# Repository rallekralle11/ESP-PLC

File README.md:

# ESP-PLC
Mostly designed this to learn more about PLCs myself. It's not made to any indistrial standard as i can't even afford those standards documents.

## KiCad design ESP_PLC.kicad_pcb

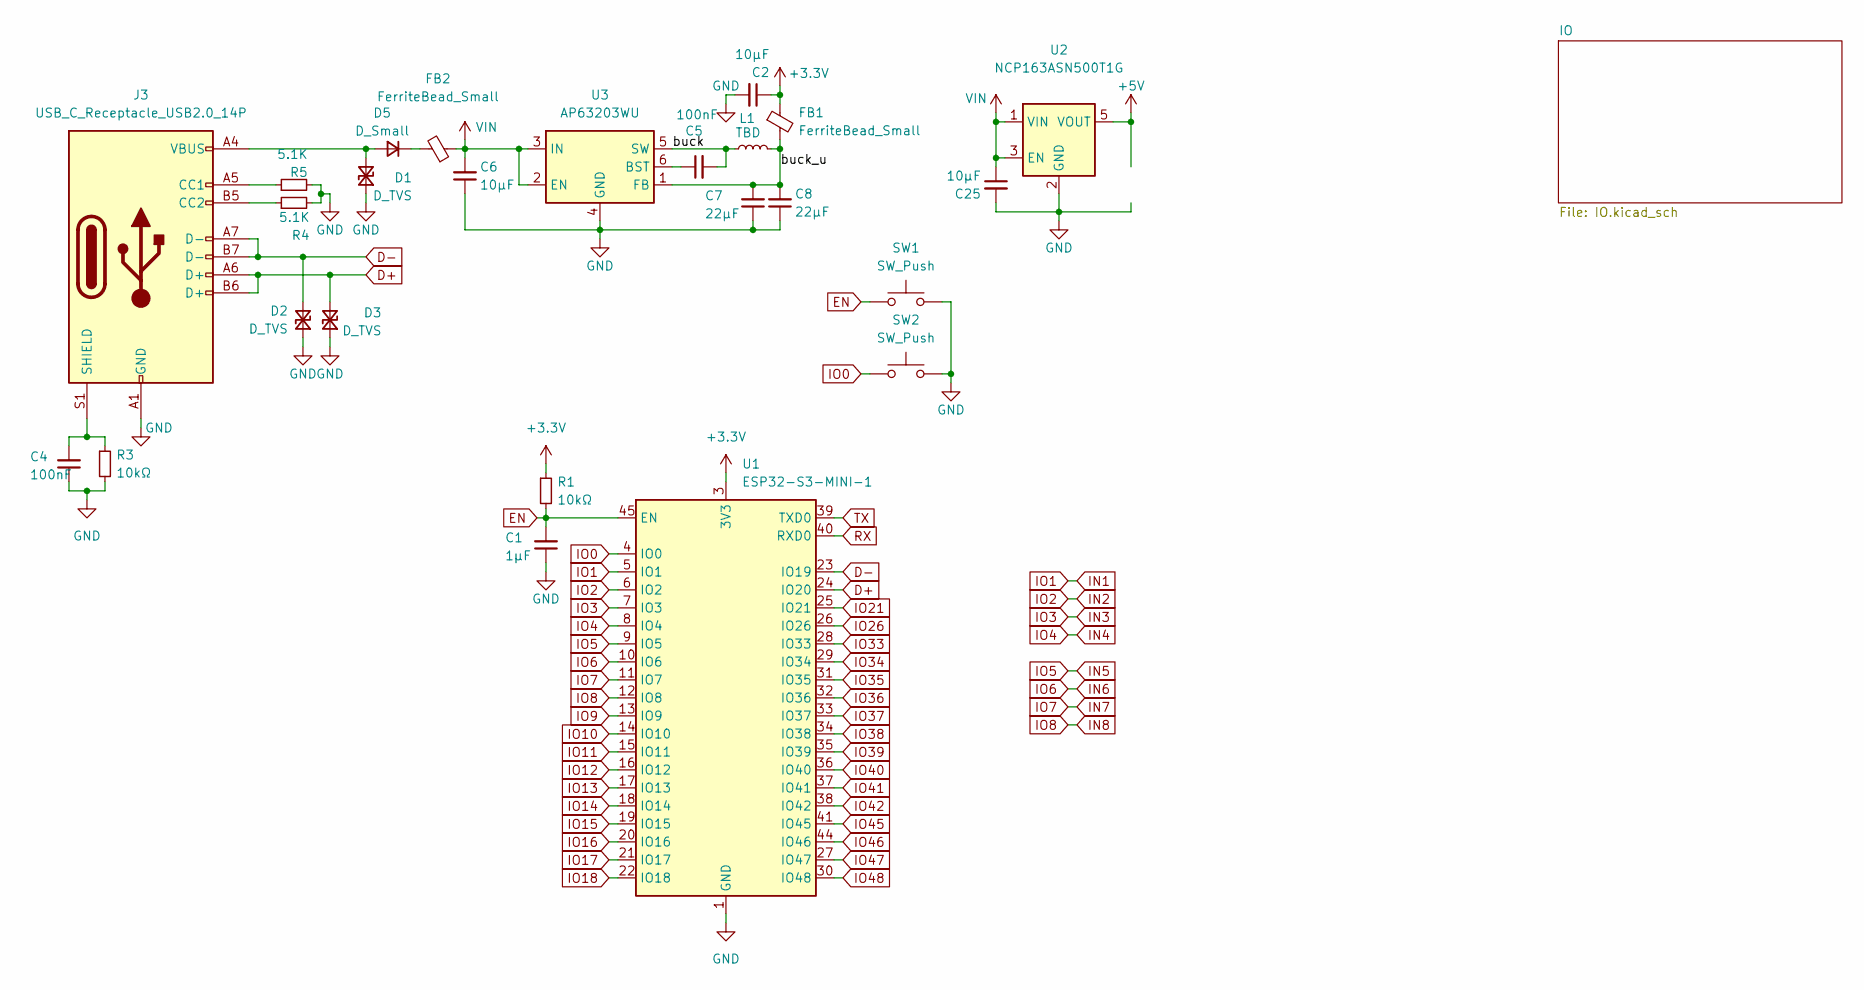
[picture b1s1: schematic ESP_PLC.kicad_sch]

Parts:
C1: 1µF; C_0402_1005Metric
C2, C6, C25: 10µF; C_0805_2012Metric
C4, C5: 100nF; C_0402_1005Metric
C7, C8: 22µF; C_0805_2012Metric
D1, D2, D3: D_TVS; TVS_dubbel
D5: D_Small; D_SOD-323
FB1, FB2: FerriteBead_Small; L_0402_1005Metric
J3: USB_C_Receptacle_USB2.0_14P; USB_C_Receptacle_G-Switch_GT-USB-7010ASV
L1: TBD; L_Abracon_ASPI-0425
R1, R3: 10kΩ; R_0402_1005Metric
R4, R5: 5.1K; R_0402_1005Metric
SW1, SW2: SW_Push; SW_Push_SPST_NO_Alps_SKRK
U1: ESP32-S3-MINI-1; ESP32-S2-MINI-1
U2: NCP163ASN500T1G; SOT-23-5
U3: AP63203WU; TSOT-23-6

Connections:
+3.3V: C2.1, FB1.1, R1.1, U1.3 (3V3); also elsewhere on the board
+5V: U2.5 (VOUT); also elsewhere on the board
/buck: C5.2, L1.1, U3.5 (SW)
/buck_u: C7.2, C8.2, FB1.2, L1.2, U3.1 (FB)
D+: D3.2 (A2), J3.A6 (D+), J3.B6 (D+), U1.24 (IO20)
D-: D2.2 (A2), J3.A7 (D-), J3.B7 (D-), U1.23 (IO19)
EN: C1.2, R1.2, SW1.1, U1.45 (EN)
GND: C1.1, C2.2, C4.1, C6.1, C7.1, C8.1, C25.2, D1.1 (A1), D2.1 (A1), D3.1 (A1), J3.A1 (GND), J3.A12 (GND), J3.B1 (GND), J3.B12 (GND), R3.2, R4.2, R5.2, SW1.2, SW2.2, U1.1 (GND), U1.2 (GND), U1.42 (GND), U1.43 (GND), U1.46 (GND), U1.47 (GND), U1.48 (GND), U1.49 (GND), U1.50 (GND), U1.51 (GND), U1.52 (GND), U1.53 (GND), U1.54 (GND), U1.55 (GND), U1.56 (GND), U1.57 (GND), U1.58 (GND), U1.59 (GND), U1.60 (GND), U1.61 (GND), U1.62 (GND), U1.63 (GND), U1.64 (GND), U1.65 (GND), U2.2 (GND), U3.4 (GND); also elsewhere on the board
IN1: U1.5 (IO1); also elsewhere on the board
IN2: U1.6 (IO2); also elsewhere on the board
IN3: U1.7 (IO3); also elsewhere on the board
IN4: U1.8 (IO4); also elsewhere on the board
IN5: U1.9 (IO5); also elsewhere on the board
IN6: U1.10 (IO6); also elsewhere on the board
IN7: U1.11 (IO7); also elsewhere on the board
IN8: U1.12 (IO8); also elsewhere on the board
IO0: SW2.1, U1.4 (IO0)
IO9: U1.13 (IO9)
IO10: U1.14 (IO10); also elsewhere on the board
IO11: U1.15 (IO11); also elsewhere on the board
IO12: U1.16 (IO12); also elsewhere on the board
IO13: U1.17 (IO13); also elsewhere on the board
IO14: U1.18 (IO14)
IO15: U1.19 (IO15); also elsewhere on the board
IO16: U1.20 (IO16); also elsewhere on the board
IO17: U1.21 (IO17); also elsewhere on the board
IO18: U1.22 (IO18); also elsewhere on the board
IO21: U1.25 (IO21)
IO26: U1.26 (IO26)
IO33: U1.28 (IO33)
IO34: U1.29 (IO34)
IO35: U1.31 (IO35); also elsewhere on the board
IO36: U1.32 (IO36); also elsewhere on the board
IO37: U1.33 (IO37); also elsewhere on the board
IO38: U1.34 (IO38); also elsewhere on the board
IO39: U1.35 (IO39)
IO40: U1.36 (IO40)
IO41: U1.37 (IO41)
IO42: U1.38 (IO42)
IO45: U1.41 (IO45)
IO46: U1.44 (IO46)
IO47: U1.27 (IO47); also elsewhere on the board
IO48: U1.30 (IO48)
unnamed: D1.2 (A2), D5.2 (A), J3.A4 (VBUS), J3.A9 (VBUS), J3.B4 (VBUS), J3.B9 (VBUS)
unnamed: D5.1 (K), FB2.2
unnamed: J3.A5 (CC1), R5.1
unnamed: J3.B5 (CC2), R4.1
unnamed: C4.2, J3.S1 (SHIELD), R3.1
unnamed: C5.1, U3.6 (BST)
RX: U1.40 (RXD0); also elsewhere on the board
TX: U1.39 (TXD0); also elsewhere on the board
VIN: C6.2, C25.1, FB2.1, U2.1 (VIN), U2.3 (EN), U3.2 (EN), U3.3 (IN); also elsewhere on the board

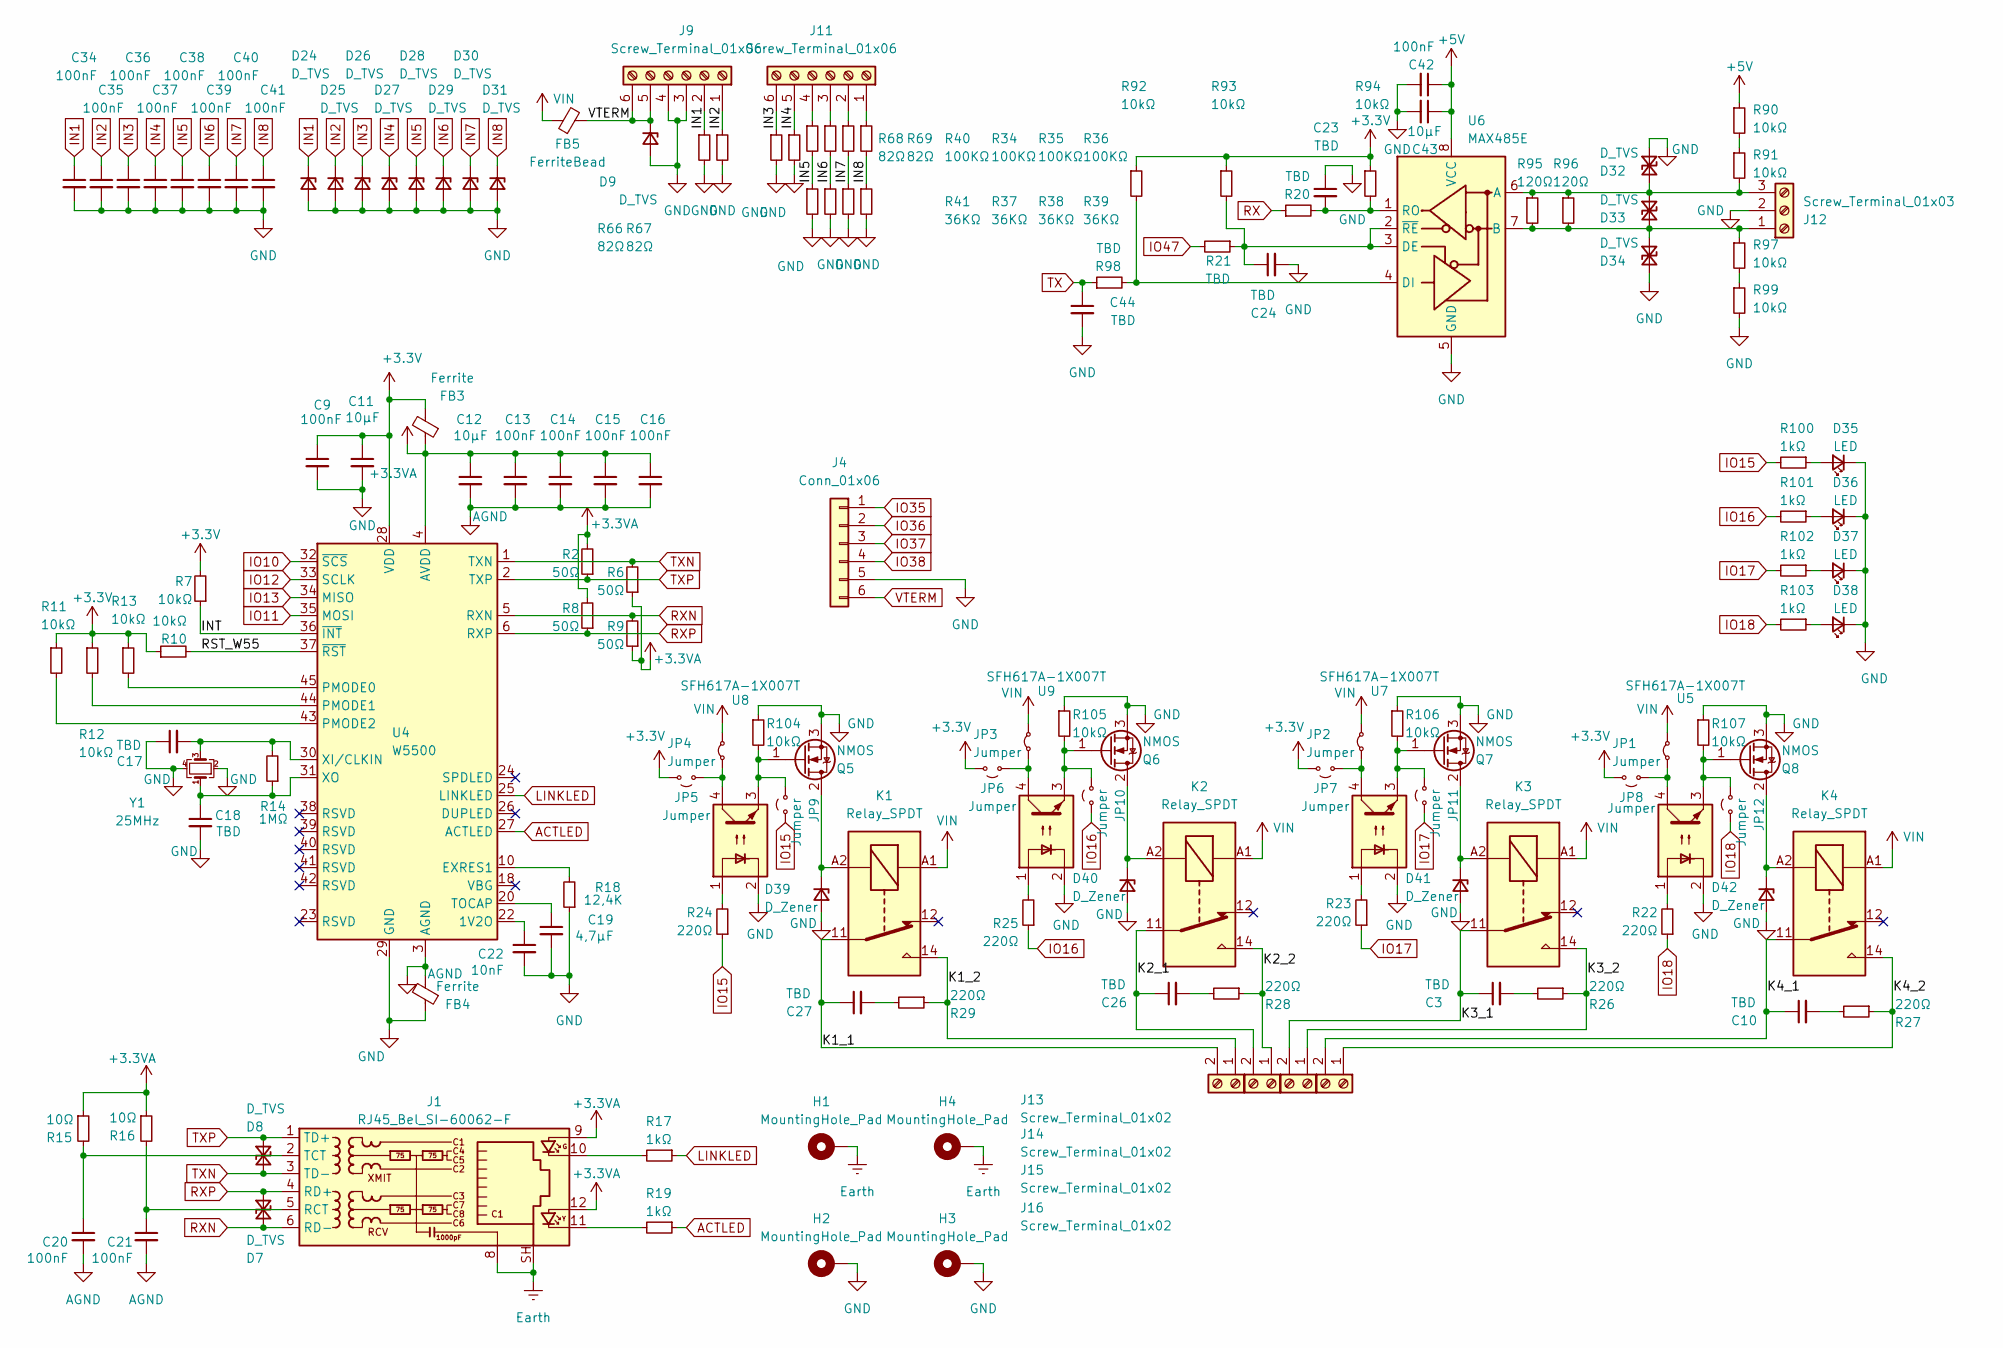
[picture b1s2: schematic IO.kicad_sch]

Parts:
C3, C10, C26, C27: TBD; C_1206_3216Metric
C9, C13, C14, C15, C16, C20, C21, C34, C35, C36, C37, C38, C39, C40, C41, C42: 100nF; C_0402_1005Metric
C11, C12, C43: 10µF; C_0805_2012Metric
C17, C18, C23, C24, C44: TBD; C_0402_1005Metric
C19: 4,7µF; C_0805_2012Metric
C22: 10nF; C_0402_1005Metric
D7, D8, D9, D24, D25, D26, D27, D28, D29, D30, D31, D32, D33, D34: D_TVS; TVS_dubbel
D35, D36, D37, D38: LED; LED_D3.0mm
D39, D40, D41, D42: D_Zener; D_SOD-323
FB3, FB4: Ferrite; L_0402_1005Metric
FB5: FerriteBead; L_0402_1005Metric
H1, H2, H3, H4: MountingHole_Pad; MountingHole_3.2mm_M3
J1: RJ45_Bel_SI-60062-F; RJ45_BEL_SS74301-00x_Vertical
J4: Conn_01x06; PinSocket_1x06_P2.54mm_Vertical
J9, J11: Screw_Terminal_01x06; TerminalBlock_MaiXu_MX126-5.0-06P_1x06_P5.00mm
J12: Screw_Terminal_01x03; TerminalBlock_MaiXu_MX126-5.0-03P_1x03_P5.00mm
J13, J14, J15, J16: Screw_Terminal_01x02; TerminalBlock_MaiXu_MX126-5.0-02P_1x02_P5.00mm
JP1, JP2, JP3, JP4: Jumper; SolderJumper-2_P1.3mm_Bridged_RoundedPad1.0x1.5mm
JP5, JP6, JP7, JP8, JP9, JP10, JP11, JP12: Jumper; SolderJumper-2_P1.3mm_Open_RoundedPad1.0x1.5mm
K1, K2, K3, K4: Relay_SPDT; Relay_SPDT_Hongfa_HF3F-L-xx-1ZL1T
Q5, Q6, Q7, Q8: NMOS; SOT-23-3
R2, R6, R8, R9: 50Ω; R_0402_1005Metric
R7, R10, R11, R12, R13, R90, R91, R92, R93, R94, R97, R99, R104, R105, R106, R107: 10kΩ; R_0402_1005Metric
R14: 1MΩ; R_0402_1005Metric
R15, R16: 10Ω; R_0402_1005Metric
R17, R19, R100, R101, R102, R103: 1kΩ; R_0402_1005Metric
R18: 12,4K; R_0402_1005Metric
R20, R21, R98: TBD; R_0402_1005Metric
R22, R23, R24, R25: 220Ω; R_0402_1005Metric
R26, R27, R28, R29: 220Ω; R_1206_3216Metric
R34, R35, R36, R40: 100KΩ; R_0402_1005Metric
R37, R38, R39, R41: 36KΩ; R_0402_1005Metric
R66, R67, R68, R69: 82Ω; R_0402_1005Metric
R95, R96: 120Ω; R_0402_1005Metric
U4: W5500; LQFP-48_7x7mm_P0.5mm
U5, U7, U8, U9: SFH617A-1X007T; SOP-4_4.4x2.6mm_P1.27mm
U6: MAX485E; SOIC-8_3.9x4.9mm_P1.27mm
Y1: 25MHz; Crystal_SMD_3225-4Pin_3.2x2.5mm

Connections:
+3.3V: C9.1, C11.1, FB3.2, JP5.2 (B), JP6.2 (B), JP7.2 (B), JP8.2 (B), R7.2, R10.1, R11.1, R12.1, R13.1, R92.1, R93.1, R94.1, U4.28 (VDD); also elsewhere on the board
+3.3VA: C12.1, C13.1, C14.1, C15.1, C16.1, FB3.1, J1.9, J1.12, R2.2, R6.1, R8.2, R9.1, R15.1, R16.1, U4.4 (AVDD), U4.8 (AVDD), U4.11 (AVDD), U4.15 (AVDD), U4.17 (AVDD), U4.21 (AVDD)
+5V: C42.1, C43.1, R90.1, U6.8 (VCC); also elsewhere on the board
/IO/INT: R7.1, U4.36 (~INT)
/IO/K1_1: C27.1, J13.2, K1.11
/IO/K1_2: J13.1, K1.14, R29.1
/IO/K2_1: C26.1, J14.2, K2.11
/IO/K2_2: J14.1, K2.14, R28.1
/IO/K3_1: C3.1, J15.2, K3.11
/IO/K3_2: J15.1, K3.14, R26.1
/IO/K4_1: C10.1, J16.2, K4.11
/IO/K4_2: J16.1, K4.14, R27.1
/IO/RST_W55: R10.2, U4.37 (~RST)
ACTLED: R19.1, U4.27 (ACTLED)
AGND: C12.2, C13.2, C14.2, C15.2, C16.2, C20.2, C21.2, FB4.2, U4.3 (AGND), U4.9 (AGND), U4.14 (AGND), U4.16 (AGND), U4.19 (AGND), U4.48 (AGND)
Earth: H1.1, H4.1, J1.8, J1.SH
GND: C9.2, C11.2, C17.1, C18.2, C19.2, C22.2, C23.1, C24.2, C34.2, C35.2, C36.2, C37.2, C38.2, C39.2, C40.2, C41.2, C42.2, C43.2, C44.2, D9.2 (A), D24.2 (A), D25.2 (A), D26.2 (A), D27.2 (A), D28.2 (A), D29.2 (A), D30.2 (A), D31.2 (A), D32.1 (A1), D34.2 (A2), D35.1 (K), D36.1 (K), D37.1 (K), D38.1 (K), D39.2 (A), D40.2 (A), D41.2 (A), D42.2 (A), FB4.1, H2.1, H3.1, J4.5, J9.3, J9.4, J12.2, Q5.3 (S), Q6.3 (S), Q7.3 (S), Q8.3 (S), R18.1, R37.2, R38.2, R39.2, R41.2, R66.2, R67.2, R68.2, R69.2, R99.2, R104.1, R105.1, R106.1, R107.1, U4.29 (GND), U5.2, U6.5 (GND), U7.2, U8.2, U9.2, Y1.2, Y1.4; also elsewhere on the board
IN1: C34.1, D24.1 (K), J9.2, R66.1; also elsewhere on the board
IN2: C35.1, D25.1 (K), J9.1, R67.1; also elsewhere on the board
IN3: C36.1, D26.1 (K), J11.6, R68.1; also elsewhere on the board
IN4: C37.1, D27.1 (K), J11.5, R69.1; also elsewhere on the board
IN5: C38.1, D28.1 (K), R40.2, R41.1; also elsewhere on the board
IN6: C39.1, D29.1 (K), R34.2, R37.1; also elsewhere on the board
IN7: C40.1, D30.1 (K), R35.2, R38.1; also elsewhere on the board
IN8: C41.1, D31.1 (K), R36.2, R39.1; also elsewhere on the board
IO10: U4.32 (~SCS); also elsewhere on the board
IO11: U4.35 (MOSI); also elsewhere on the board
IO12: U4.33 (SCLK); also elsewhere on the board
IO13: U4.34 (MISO); also elsewhere on the board
IO15: JP9.1 (A), R24.1, R100.2; also elsewhere on the board
IO16: JP10.1 (A), R25.1, R101.2; also elsewhere on the board
IO17: JP11.1 (A), R23.1, R102.2; also elsewhere on the board
IO18: JP12.1 (A), R22.1, R103.2; also elsewhere on the board
IO35: J4.1; also elsewhere on the board
IO36: J4.2; also elsewhere on the board
IO37: J4.3; also elsewhere on the board
IO38: J4.4; also elsewhere on the board
IO47: R21.2; also elsewhere on the board
LINKLED: R17.1, U4.25 (LINKLED)
unnamed: C3.2, R26.2
unnamed: C10.2, R27.2
unnamed: C26.2, R28.2
unnamed: C27.2, R29.2
unnamed: D32.2 (A2), D33.1 (A1), J12.3, R91.2, R95.1, R96.1, U6.6 (A)
unnamed: D33.2 (A2), D34.1 (A1), J12.1, R95.2, R96.2, R97.1, U6.7 (B)
unnamed: D35.2 (A), R100.1
unnamed: D36.2 (A), R101.1
unnamed: D37.2 (A), R102.1
unnamed: D38.2 (A), R103.1
unnamed: D39.1 (K), K1.A2, Q5.2 (D)
unnamed: D40.1 (K), K2.A2, Q6.2 (D)
unnamed: D41.1 (K), K3.A2, Q7.2 (D)
unnamed: D42.1 (K), K4.A2, Q8.2 (D)
unnamed: J1.10, R17.2
unnamed: J1.11, R19.2
unnamed: C21.1, J1.5 (RCT), R16.2
unnamed: C20.1, J1.2 (TCT), R15.2
unnamed: J11.1, R36.1
unnamed: J11.2, R35.1
unnamed: J11.3, R34.1
unnamed: J11.4, R40.1
unnamed: JP1.1 (A), JP8.1 (A), U5.4
unnamed: JP2.1 (A), JP7.1 (A), U7.4
unnamed: JP3.1 (A), JP6.1 (A), U9.4
unnamed: JP4.1 (A), JP5.1 (A), U8.4
unnamed: JP9.2 (B), Q5.1 (G), R104.2, U8.3
unnamed: JP10.2 (B), Q6.1 (G), R105.2, U9.3
unnamed: JP11.2 (B), Q7.1 (G), R106.2, U7.3
unnamed: JP12.2 (B), Q8.1 (G), R107.2, U5.3
unnamed: R22.2, U5.1
unnamed: R23.2, U7.1
unnamed: R24.2, U8.1
unnamed: R25.2, U9.1
unnamed: R90.2, R91.1
unnamed: R97.2, R99.1
unnamed: C22.1, U4.22 (1V2O)
unnamed: R18.2, U4.10 (EXRES1)
unnamed: R13.2, U4.45 (PMODE0)
unnamed: R12.2, U4.44 (PMODE1)
unnamed: R11.2, U4.43 (PMODE2)
unnamed: C19.1, U4.20 (TOCAP)
unnamed: C17.2, R14.2, U4.30 (XI/CLKIN), Y1.3
unnamed: C18.1, R14.1, U4.31 (XO), Y1.1
unnamed: C24.1, R21.1, R93.2, U6.2 (~RE), U6.3 (DE)
unnamed: R92.2, R98.2, U6.4 (DI)
unnamed: C23.2, R20.2, R94.2, U6.1 (RO)
RX: R20.1; also elsewhere on the board
RXN: D7.2 (A2), J1.6 (RD-), R9.2, U4.5 (RXN)
RXP: D7.1 (A1), J1.4 (RD+), R8.1, U4.6 (RXP)
TX: C44.1, R98.1; also elsewhere on the board
TXN: D8.2 (A2), J1.3 (TD-), R6.2, U4.1 (TXN)
TXP: D8.1 (A1), J1.1 (TD+), R2.1, U4.2 (TXP)
VIN: FB5.1, JP1.2 (B), JP2.2 (B), JP3.2 (B), JP4.2 (B), K1.A1, K2.A1, K3.A1, K4.A1; also elsewhere on the board
VTERM: D9.1 (K), FB5.2, J4.6, J9.5, J9.6

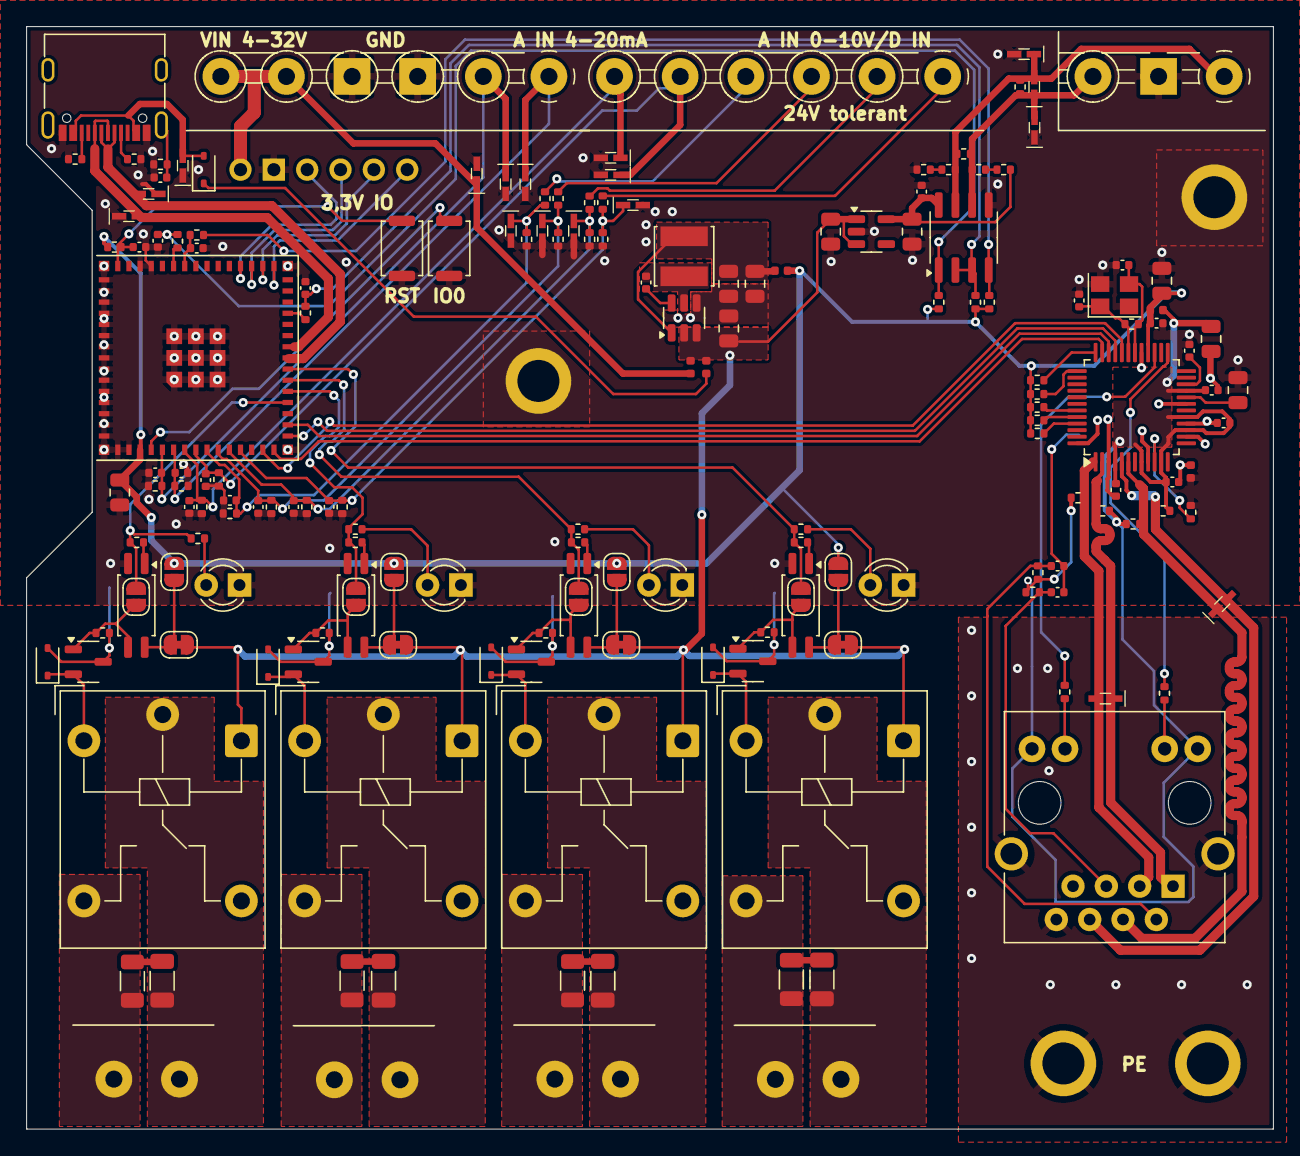
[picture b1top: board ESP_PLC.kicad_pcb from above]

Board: 2 copper layers, 95.0 x 84.0 mm, 179 parts (0 on the bottom side), 106 nets.

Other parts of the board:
R70, R71, R72, R73: 82Ω; R_0402_1005Metric

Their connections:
GND: R70.2, R71.2, R72.2, R73.2; also elsewhere on the board
IN5: R70.1; also elsewhere on the board
IN6: R71.1; also elsewhere on the board
IN7: R72.1; also elsewhere on the board
IN8: R73.1; also elsewhere on the board

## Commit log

2024-10-20 init
2024-11-07 development
